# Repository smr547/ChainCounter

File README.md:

# ChainCounter
Develop a chain counter for a boat. The chain counter should be fully integrated with the ship's navigation system and offer features such as

* Bright display at helm
* Display:
  * length of chain out,
  * % of total length out,
  * current scope (chainOut/depth),
  * gypsy status (idle, up, down, freefall, bound and fault condition)
* Anchor location: Home, dangling, dropping, lifting, free falling, on bottom, set
* Anchor last known position (latitude, longitude and depth -- in case the anchor and chain are lost)
* Automatic anchor watch activation and cancellation
* Notifications
** Deploying anchor
** Anchor on bottom
** Anchor holding
** Lifting anchor
** Anchor weighed
** Anchor homed
* Voice notification and warnings
* Alarms and warnings:
** end of chain,
** insufficient scope,
** bound gypsy,
** anchor dragging,
** boat left anchor zone
* All information available remotely (web page and mobile app)
* Remote control of windlass (up / down buttons)
* Parameters configurable via web page (gypsy circumference, chain length, alarm limits, anchor watch safety factor)
* Integration via open RESTful interface

The Chain counter should be engineered using Open Source software and hardware to keep costs down and allow it to be easily integrated with other on-board systems.

## Parameters reported

* ``navigation.anchor.chainOut`` -- length of chain out
* ``navigation.anchor.chainPercent`` -- chain out as a percentage of chain available
* ``navigation.anchor.gypsyStatus`` -- idle, up, down, freefall, bound, fault(code)
* ``navigation.anchor.deploymentStatus`` -- home, hanging, inWater, onBottom or unknown (depth data unavailable)
* ``navigation.anchor.bottomPosition`` -- lat/long of anchor on bottom (if depth and GPS data unavailable)
* ``navigation.anchor.scopeOut`` -- chain out as a factor of depth (if depth data unavailable)
* ``navigation.anchor.gypsyCircumference`` -- circumference of gypsy *
* ``navigation.anchor.chainLength`` -- length of chain installed *

(* indicates parameter configurable via web page or RESTful interface)

## Events reported

* chain stopped / moving
* chain on bottom
* chain weighed (off bottom)
* chain home

## Hardware Design
See the [hardware directory](./hardware) for further information. 
We are using [KiCad]([Ihttps://www.kicad.org/) for hardware design. See the [Schematic of current version](./hardware/KiCad/schematic_current_version.pdf).

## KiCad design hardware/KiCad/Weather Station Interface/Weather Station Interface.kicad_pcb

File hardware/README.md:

## Hardware

Hardware compontents of the Chain Counter

Please review the [KiCad directory](./KiCad) for hardware design documentation

## Old chain counter
The old chain counter is a Qwick CHC 1202M ([see Manual](./quick_1202M_manual.pdf))

# Test bed

A benchtop test bed has been built it comprises

## Current design

- 12V input from lead acid battery
- Windlass electromechanical emulator -- Tamiya plastic moulded gearbox and motor casing. Included is a FA-30 type 3 volt electric motor, axle with 2 crank arm's) Gearbox 344:1 reduction, approx 30 RPM.
- Reed switch and magnet on crank arm to emulate windlass chain counter pickup
- Dual relays wired as reversing relays (12V solenoid, 3.3V power distribution to windlass motor)
- UP/DOWN buttons to power reversing relays (emulating forward hand control on boat)
- 12V to 3.3V DC/DC converter to power windlass motor
- 12V to 5V DC/DC converter to power MCU and related logic
- ESP32 dev module
- 2x16 LCD display module with I2C interface
- 3 minature push buttons to emulate chain counter controls -- UP, DOWN and MENU
- 2 x resistor divider circuits providing 12V to 3.3V logic shifting to sense reversing relay solenoid state
- 2 x MOSFET driver circuits to allow chain counter logic to drive reversing relays

## Planned improvements

- replace reversing relay sence with robust, fully fitered, TVS protected sense logic (with Schmitt trigger)
- replace reed switch interface with similar filtered interface
- possibly delete MOSFET driver -- too dangerous in on-boat situation (dirving very high powered motor)
- optional configuration as "windlass sensor only" with no display (SignalK telemetry on and optional sensor pass-through to regular chain counter)

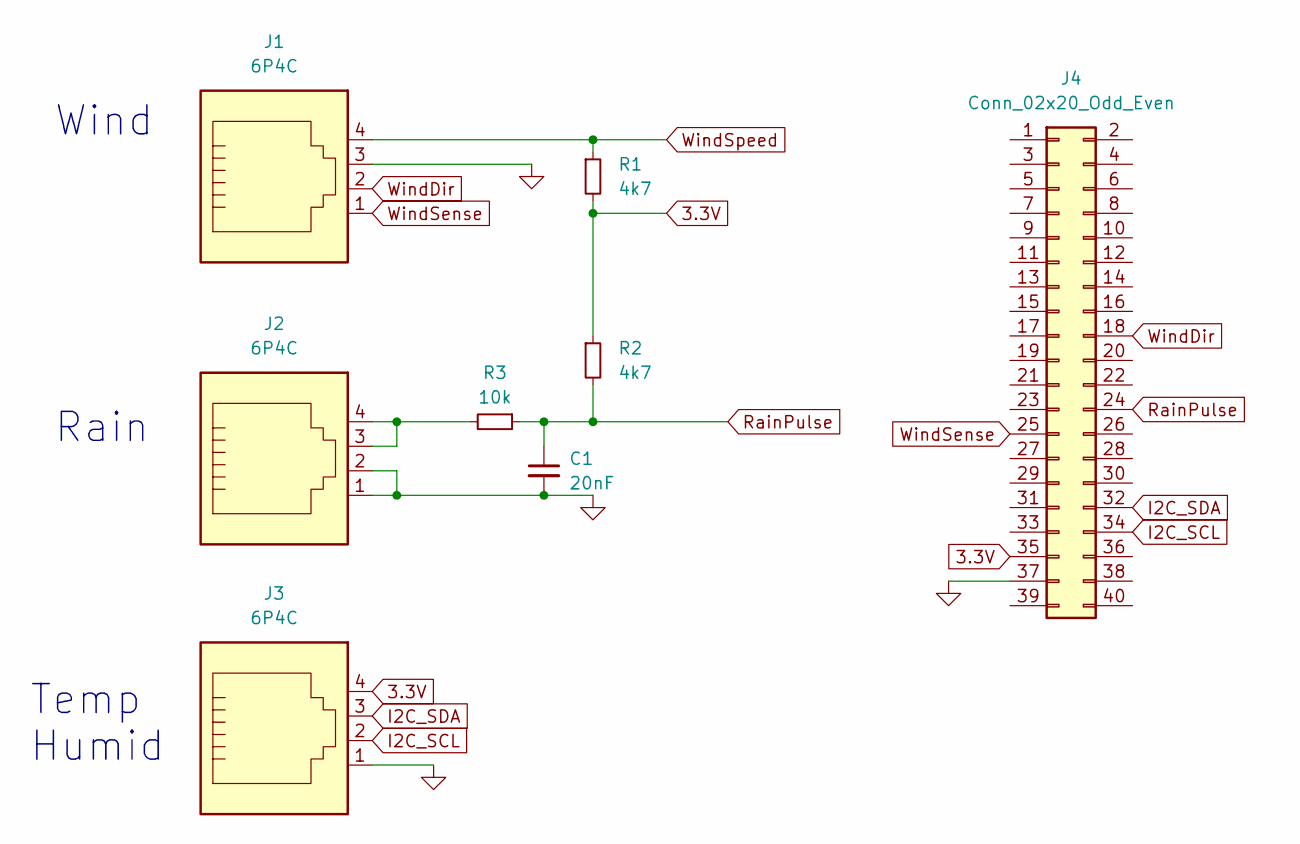
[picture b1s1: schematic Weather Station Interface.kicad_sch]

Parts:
C1: 20nF; C_1206_3216Metric_Pad1.33x1.80mm_HandSolder
J1, J2, J3: 6P4C; RJ14_Connfly_DS1133-S4_Horizontal
J4: Conn_02x20_Odd_Even; PinSocket_2x20_P2.54mm_Vertical
R1, R2: 4k7; R_0805_2012Metric_Pad1.20x1.40mm_HandSolder
R3: 10k; R_0805_2012Metric_Pad1.20x1.40mm_HandSolder

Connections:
3.3V: J3.4, J4.35, R1.2, R2.1
GND: C1.2, J1.3, J2.1, J2.2, J3.1, J4.37
I2C_SCL: J3.2, J4.34
I2C_SDA: J3.3, J4.32
unnamed: J2.3, J2.4, R3.2
RainPulse: C1.1, J4.24, R2.2, R3.1
WindDir: J1.2, J4.18
WindSense: J1.1, J4.25
WindSpeed: J1.4, R1.1

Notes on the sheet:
Wind
Rain
Temp Humid

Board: 2 copper layers, 8 parts (1 on the bottom side), 9 nets, no tracks yet.

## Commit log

2024-01-11 Setup for vscode and Platformio
2024-01-17 Minor change for OLED display demo
2024-01-17 Initial hardware design using KiCad
2024-01-17 Hardware comments in README file
2024-01-17 ignore lock files
2024-01-17 Photos of old chain counter
2024-01-17 Add chain counter manual
2024-01-18 Initial QM model
2024-01-18 Ignore generated code files
2024-05-19 Hardware design files and state charts
2024-05-19 remove platormio.ini
2024-05-19 Remove QuantumLeaps model file
2024-05-19 Remove remnants of QuantumLeaps modelling
2024-05-19 Bring in new code
2024-05-19 Remove unnecessary file
2024-05-19 Editor config files
2026-01-23 doco and hardware design fix
2026-01-23 Add emulator photo
2026-01-23 Add windlass emulator image to README
    Added image of the windlass emulator to the README.
2026-01-23 Fix image extension for windlass emulator
    Updated image file extension from .jpg to .jpeg in README.
